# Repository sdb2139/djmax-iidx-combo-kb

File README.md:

# djmax-iidx-combo-kb
PCB (and firmware eventually) for a combo DJMax/EZ2ON and IIDX keyboard using an Arduino Pro Micro

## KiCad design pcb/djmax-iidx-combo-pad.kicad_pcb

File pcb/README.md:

This folder will contain the files for the PCB as well as the schematic.  As files are uploaded I will add a short summary of them.

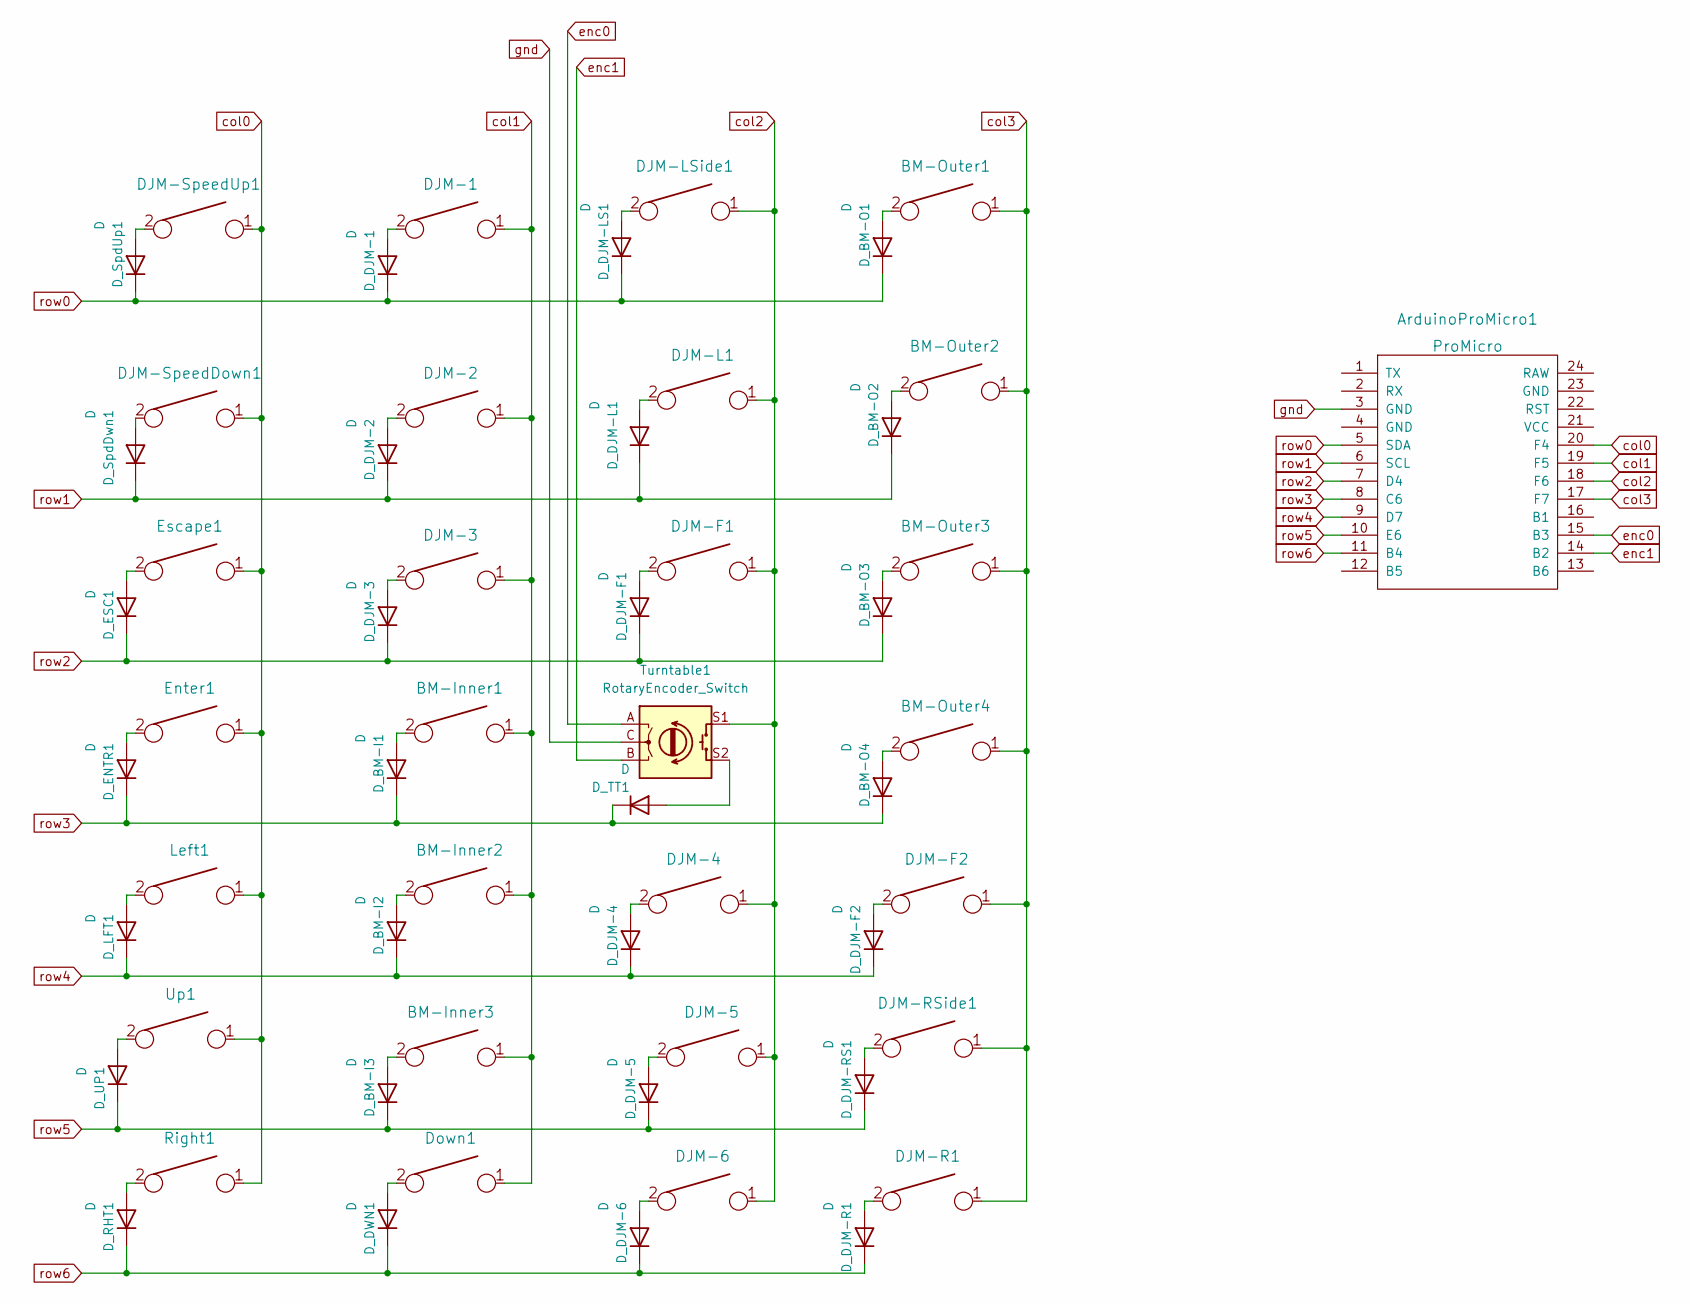
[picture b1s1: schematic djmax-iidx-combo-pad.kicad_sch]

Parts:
ArduinoProMicro1: ProMicro
BM-Inner1, BM-Inner2, BM-Inner3: KEYSW; SW_Cherry_MX_2.00u_Vertical_PCB
BM-Outer1, BM-Outer2, BM-Outer3, BM-Outer4: KEYSW; SW_Cherry_MX_2.00u_Vertical_PCB
DJM-1, DJM-2, DJM-3, DJM-4, DJM-5, DJM-6: KEYSW; SW_Cherry_MX_1.00u_PCB
DJM-F1, DJM-F2: KEYSW; SW_Cherry_MX_1.00u_PCB
DJM-L1: KEYSW; SW_Cherry_MX_1.00u_PCB
DJM-LSide1: KEYSW; SW_Cherry_MX_2.00u_PCB
DJM-R1: KEYSW; SW_Cherry_MX_1.00u_PCB
DJM-RSide1: KEYSW; SW_Cherry_MX_2.00u_PCB
DJM-SpeedDown1: KEYSW; SW_Cherry_MX_1.00u_PCB
DJM-SpeedUp1: KEYSW; SW_Cherry_MX_1.00u_PCB
D_BM-I1, D_BM-I2, D_BM-I3: D; D_SOD123_axial
D_BM-O1, D_BM-O2, D_BM-O3, D_BM-O4: D; D_SOD123_axial
D_DJM-1, D_DJM-2, D_DJM-3, D_DJM-4, D_DJM-5, D_DJM-6: D; D_SOD123_axial
D_DJM-F1, D_DJM-F2: D; D_SOD123_axial
D_DJM-L1: D; D_SOD123_axial
D_DJM-LS1: D; D_SOD123_axial
D_DJM-R1: D; D_SOD123_axial
D_DJM-RS1: D; D_SOD123_axial
D_DWN1: D; D_SOD123_axial
D_ENTR1: D; D_SOD123_axial
D_ESC1: D; D_SOD123_axial
D_LFT1: D; D_SOD123_axial
D_RHT1: D; D_SOD123_axial
D_SpdDwn1: D; D_SOD123_axial
D_SpdUp1: D; D_SOD123_axial
D_TT1: D; D_SOD123_axial
D_UP1: D; D_SOD123_axial
Down1: KEYSW; SW_Cherry_MX_1.00u_PCB
Enter1: KEYSW; SW_Cherry_MX_1.00u_PCB
Escape1: KEYSW; SW_Cherry_MX_1.00u_PCB
Left1: KEYSW; SW_Cherry_MX_1.00u_PCB
Right1: KEYSW; SW_Cherry_MX_1.00u_PCB
Turntable1: RotaryEncoder_Switch; RotaryEncoder_Alps_EC11E-Switch_Vertical_H20mm
Up1: KEYSW; SW_Cherry_MX_1.00u_PCB

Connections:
unnamed: BM-Inner1.2, D_BM-I1.2 (A)
unnamed: BM-Inner2.2, D_BM-I2.2 (A)
unnamed: BM-Inner3.2, D_BM-I3.2 (A)
unnamed: BM-Outer1.2, D_BM-O1.2 (A)
unnamed: BM-Outer3.2, D_BM-O3.2 (A)
unnamed: BM-Outer4.2, D_BM-O4.2 (A)
unnamed: DJM-1.2, D_DJM-1.2 (A)
unnamed: DJM-2.2, D_DJM-2.2 (A)
unnamed: DJM-4.2, D_DJM-4.2 (A)
unnamed: DJM-6.2, D_DJM-6.2 (A)
unnamed: DJM-F1.2, D_DJM-F1.2 (A)
unnamed: DJM-F2.2, D_DJM-F2.2 (A)
unnamed: DJM-L1.2, D_DJM-L1.2 (A)
unnamed: DJM-LSide1.2, D_DJM-LS1.2 (A)
unnamed: DJM-R1.2, D_DJM-R1.2 (A)
unnamed: DJM-RSide1.2, D_DJM-RS1.2 (A)
unnamed: BM-Outer2.2, D_BM-O2.2 (A)
unnamed: DJM-3.2, D_DJM-3.2 (A)
unnamed: DJM-5.2, D_DJM-5.2 (A)
unnamed: D_DWN1.2 (A), Down1.2
unnamed: D_ENTR1.2 (A), Enter1.2
unnamed: D_ESC1.2 (A), Escape1.2
unnamed: D_RHT1.2 (A), Right1.2
unnamed: DJM-SpeedDown1.2, D_SpdDwn1.2 (A)
unnamed: DJM-SpeedUp1.2, D_SpdUp1.2 (A)
unnamed: D_UP1.2 (A), Up1.2
unnamed: D_LFT1.2 (A), Left1.2
unnamed: D_TT1.2 (A), Turntable1.S2
col0: ArduinoProMicro1.20 (F4), DJM-SpeedDown1.1, DJM-SpeedUp1.1, Enter1.1, Escape1.1, Left1.1, Right1.1, Up1.1
col1: ArduinoProMicro1.19 (F5), BM-Inner1.1, BM-Inner2.1, BM-Inner3.1, DJM-1.1, DJM-2.1, DJM-3.1, Down1.1
col2: ArduinoProMicro1.18 (F6), DJM-4.1, DJM-5.1, DJM-6.1, DJM-F1.1, DJM-L1.1, DJM-LSide1.1, Turntable1.S1
col3: ArduinoProMicro1.17 (F7), BM-Outer1.1, BM-Outer2.1, BM-Outer3.1, BM-Outer4.1, DJM-F2.1, DJM-R1.1, DJM-RSide1.1
enc0: ArduinoProMicro1.15 (B3), Turntable1.A
enc1: ArduinoProMicro1.14 (B2), Turntable1.B
gnd: ArduinoProMicro1.3 (GND), Turntable1.C
row0: ArduinoProMicro1.5 (SDA), D_BM-O1.1 (K), D_DJM-1.1 (K), D_DJM-LS1.1 (K), D_SpdUp1.1 (K)
row1: ArduinoProMicro1.6 (SCL), D_BM-O2.1 (K), D_DJM-2.1 (K), D_DJM-L1.1 (K), D_SpdDwn1.1 (K)
row2: ArduinoProMicro1.7 (D4), D_BM-O3.1 (K), D_DJM-3.1 (K), D_DJM-F1.1 (K), D_ESC1.1 (K)
row3: ArduinoProMicro1.8 (C6), D_BM-I1.1 (K), D_BM-O4.1 (K), D_ENTR1.1 (K), D_TT1.1 (K)
row4: ArduinoProMicro1.9 (D7), D_BM-I2.1 (K), D_DJM-4.1 (K), D_DJM-F2.1 (K), D_LFT1.1 (K)
row5: ArduinoProMicro1.10 (E6), D_BM-I3.1 (K), D_DJM-5.1 (K), D_DJM-RS1.1 (K), D_UP1.1 (K)
row6: ArduinoProMicro1.11 (B4), D_DJM-6.1 (K), D_DJM-R1.1 (K), D_DWN1.1 (K), D_RHT1.1 (K)

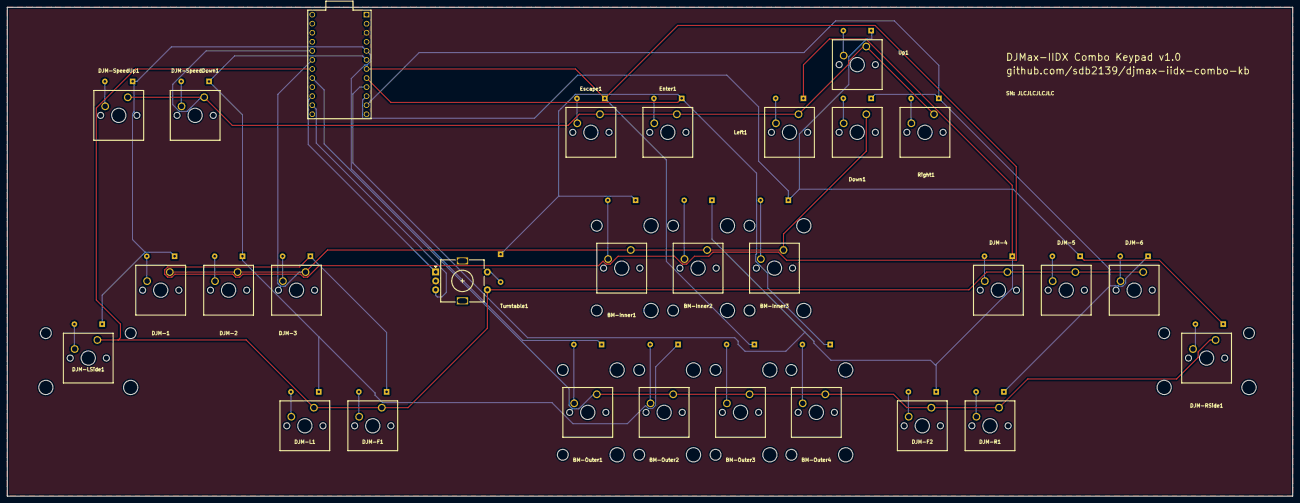
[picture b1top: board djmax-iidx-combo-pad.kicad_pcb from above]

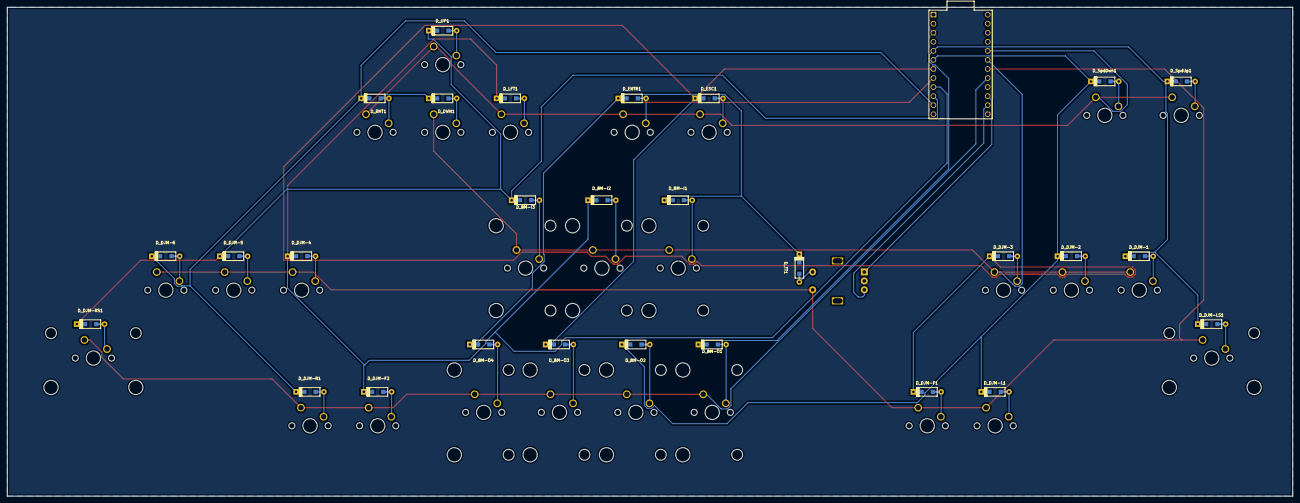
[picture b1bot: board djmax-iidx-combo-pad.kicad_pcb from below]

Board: 2 copper layers, 360.7 x 137.2 mm, 57 parts (29 on the bottom side), 42 nets.

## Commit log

2023-02-02 gerber files generated
